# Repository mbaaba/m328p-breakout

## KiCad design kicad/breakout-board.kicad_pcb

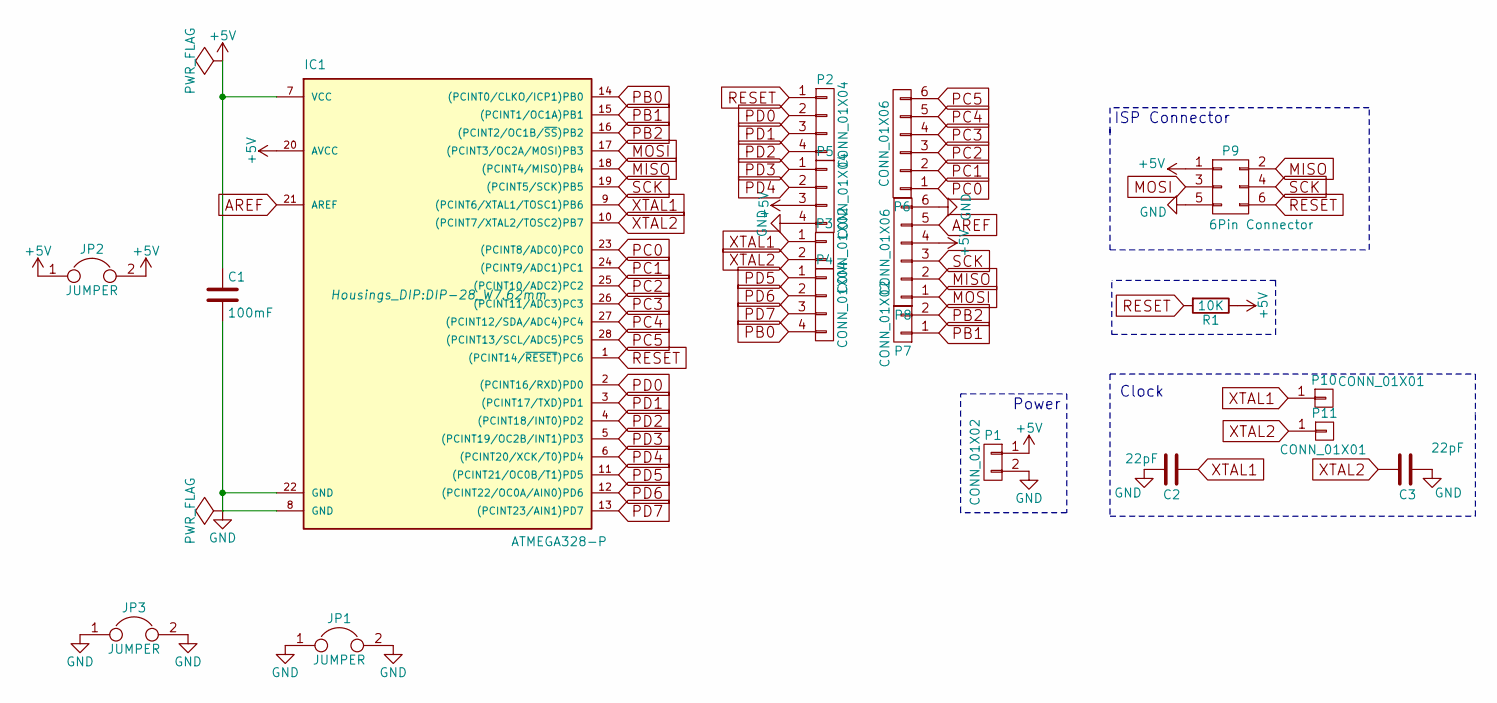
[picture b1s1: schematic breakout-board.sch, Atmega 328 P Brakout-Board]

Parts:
C1: 100mF; C_Disc_D3_P2.5
C2, C3: 22pF; C_Disc_D3_P2.5
IC1: ATMEGA328-P; DIP-28_W7.62mm
JP1, JP2, JP3: JUMPER; Resistor_Horizontal_RM15mm
P1, P3, P7: CONN_01X02; Pin_Header_Straight_1x02
P2, P4, P5: CONN_01X04; Pin_Header_Straight_1x04
P6, P8: CONN_01X06; Pin_Header_Straight_1x06
P9: 6Pin Connector; Pin_Header_Straight_2x03
P10, P11: CONN_01X01; Pin_Header_Straight_1x01
R1: 10K; Resistor_Vertical_RM5mm

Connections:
+5V: C1.1, IC1.7 (VCC), IC1.20 (AVCC), JP2.1, JP2.2, P1.1, P5.3, P8.4, P9.1, R1.1
AREF: IC1.21 (AREF), P8.5
GND: C1.2, C2.2, C3.1, IC1.8 (GND), IC1.22 (GND), JP1.1, JP1.2, JP3.1, JP3.2, P1.2, P5.4, P8.6, P9.5
MISO: IC1.18 ((PCINT4/MISO)PB4), P8.2, P9.2
MOSI: IC1.17 ((PCINT3/OC2A/MOSI)PB3), P8.1, P9.3
PB0: IC1.14 ((PCINT0/CLKO/ICP1)PB0), P4.4
PB1: IC1.15 ((PCINT1/OC1A)PB1), P7.1
PB2: IC1.16 ((PCINT2/OC1B/~SS~)PB2), P7.2
PC0: IC1.23 ((PCINT8/ADC0)PC0), P6.1
PC1: IC1.24 ((PCINT9/ADC1)PC1), P6.2
PC2: IC1.25 ((PCINT10/ADC2)PC2), P6.3
PC3: IC1.26 ((PCINT11/ADC3)PC3), P6.4
PC4: IC1.27 ((PCINT12/SDA/ADC4)PC4), P6.5
PC5: IC1.28 ((PCINT13/SCL/ADC5)PC5), P6.6
PD0: IC1.2 ((PCINT16/RXD)PD0), P2.2
PD1: IC1.3 ((PCINT17/TXD)PD1), P2.3
PD2: IC1.4 ((PCINT18/INT0)PD2), P2.4
PD3: IC1.5 ((PCINT19/OC2B/INT1)PD3), P5.1
PD4: IC1.6 ((PCINT20/XCK/T0)PD4), P5.2
PD5: IC1.11 ((PCINT21/OC0B/T1)PD5), P4.1
PD6: IC1.12 ((PCINT22/OC0A/AIN0)PD6), P4.2
PD7: IC1.13 ((PCINT23/AIN1)PD7), P4.3
RESET: IC1.1 ((PCINT14/~RESET~)PC6), P2.1, P9.6, R1.2
SCK: IC1.19 ((PCINT5/SCK)PB5), P8.3, P9.4
XTAL1: C2.1, IC1.9 ((PCINT6/XTAL1/TOSC1)PB6), P3.1, P10.1
XTAL2: C3.2, IC1.10 ((PCINT7/XTAL2/TOSC2)PB7), P3.2, P11.1

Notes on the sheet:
ISP Connector
Power
Clock

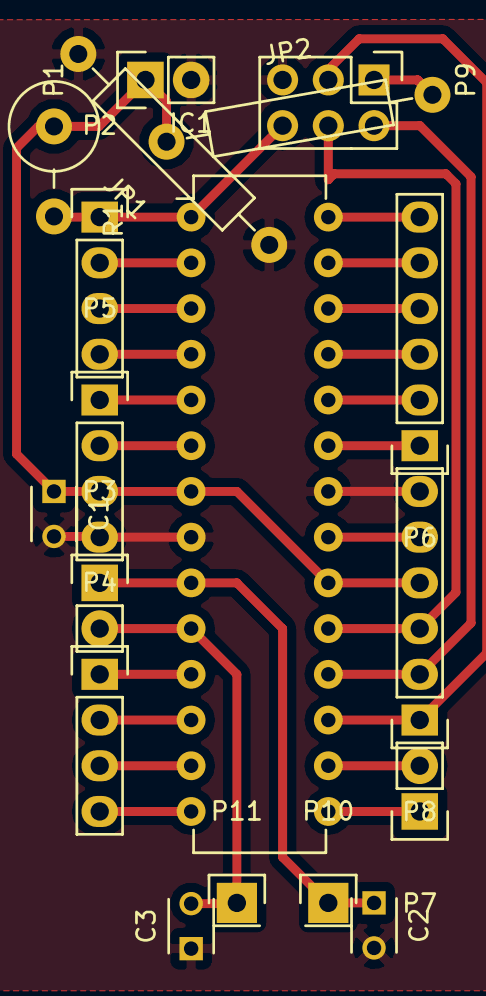
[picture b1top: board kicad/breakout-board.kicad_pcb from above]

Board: 2 copper layers, 18 parts (0 on the bottom side), 26 nets.

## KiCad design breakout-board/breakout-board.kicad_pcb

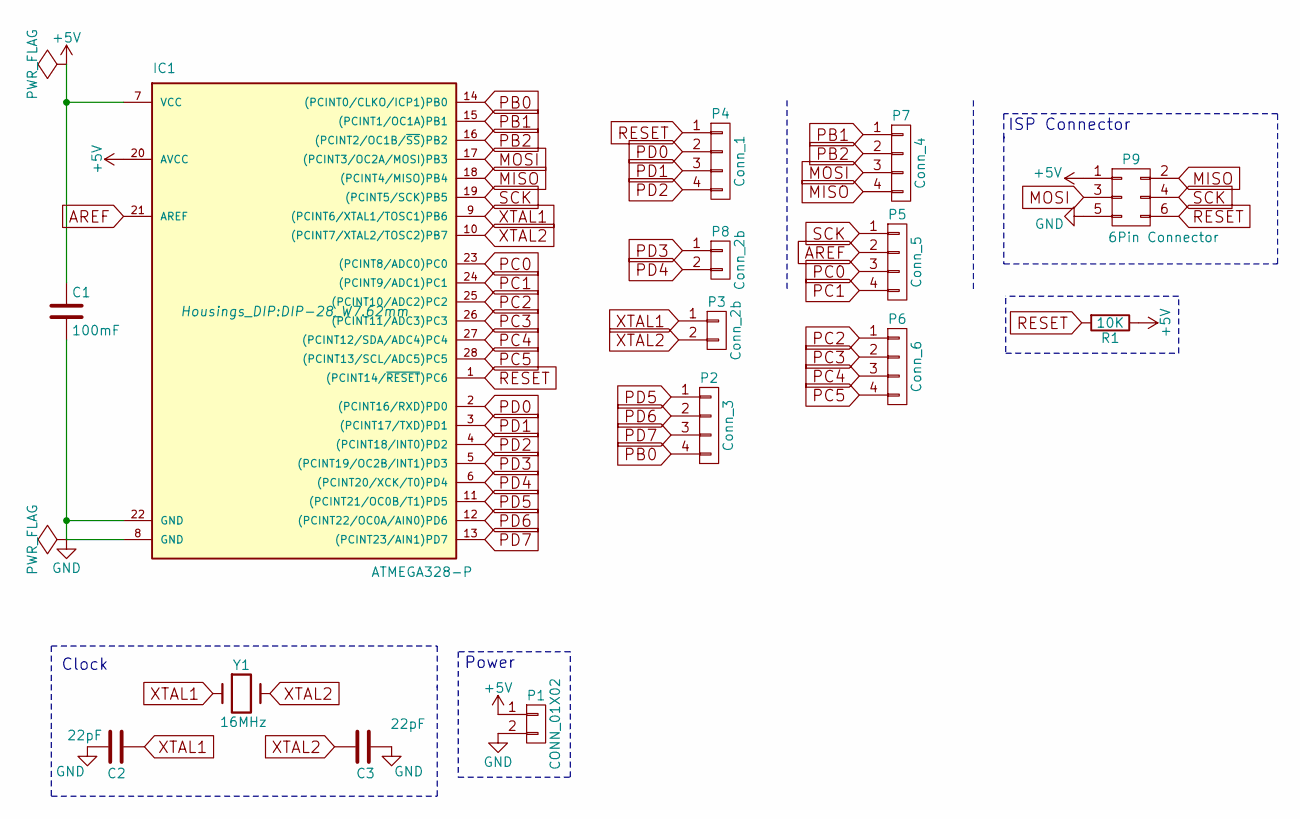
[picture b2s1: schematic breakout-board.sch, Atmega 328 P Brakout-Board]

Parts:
C1: 100mF; C_Disc_D3_P2.5
C2, C3: 22pF; C_Disc_D3_P2.5
IC1: ATMEGA328-P; DIP-28_W7.62mm
P1: CONN_01X02; Pin_Header_Straight_1x02
P2: Conn_3; Pin_Header_Straight_1x04
P3, P8: Conn_2b; Pin_Header_Straight_1x02
P4: Conn_1; Pin_Header_Straight_1x04
P5: Conn_5; Pin_Header_Straight_1x04
P6: Conn_6; Pin_Header_Straight_1x04
P7: Conn_4; Pin_Header_Straight_1x04
P9: 6Pin Connector; Pin_Header_Straight_2x03
R1: 10K; Resistor_Vertical_RM5mm
Y1: 16MHz; Crystal_HC50-U_Vertical

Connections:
+5V: C1.1, IC1.7 (VCC), IC1.20 (AVCC), P1.1, P9.1, R1.1
AREF: IC1.21 (AREF), P5.2
GND: C1.2, C2.2, C3.1, IC1.8 (GND), IC1.22 (GND), P1.2, P9.5
MISO: IC1.18 ((PCINT4/MISO)PB4), P7.4, P9.2
MOSI: IC1.17 ((PCINT3/OC2A/MOSI)PB3), P7.3, P9.3
PB0: IC1.14 ((PCINT0/CLKO/ICP1)PB0), P2.4
PB1: IC1.15 ((PCINT1/OC1A)PB1), P7.1
PB2: IC1.16 ((PCINT2/OC1B/~SS~)PB2), P7.2
PC0: IC1.23 ((PCINT8/ADC0)PC0), P5.3
PC1: IC1.24 ((PCINT9/ADC1)PC1), P5.4
PC2: IC1.25 ((PCINT10/ADC2)PC2), P6.1
PC3: IC1.26 ((PCINT11/ADC3)PC3), P6.2
PC4: IC1.27 ((PCINT12/SDA/ADC4)PC4), P6.3
PC5: IC1.28 ((PCINT13/SCL/ADC5)PC5), P6.4
PD0: IC1.2 ((PCINT16/RXD)PD0), P4.2
PD1: IC1.3 ((PCINT17/TXD)PD1), P4.3
PD2: IC1.4 ((PCINT18/INT0)PD2), P4.4
PD3: IC1.5 ((PCINT19/OC2B/INT1)PD3), P8.1
PD4: IC1.6 ((PCINT20/XCK/T0)PD4), P8.2
PD5: IC1.11 ((PCINT21/OC0B/T1)PD5), P2.1
PD6: IC1.12 ((PCINT22/OC0A/AIN0)PD6), P2.2
PD7: IC1.13 ((PCINT23/AIN1)PD7), P2.3
RESET: IC1.1 ((PCINT14/~RESET~)PC6), P4.1, P9.6, R1.2
SCK: IC1.19 ((PCINT5/SCK)PB5), P5.1, P9.4
XTAL1: C2.1, IC1.9 ((PCINT6/XTAL1/TOSC1)PB6), P3.1, Y1.1
XTAL2: C3.2, IC1.10 ((PCINT7/XTAL2/TOSC2)PB7), P3.2, Y1.2

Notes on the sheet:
ISP Connector
Power
Clock

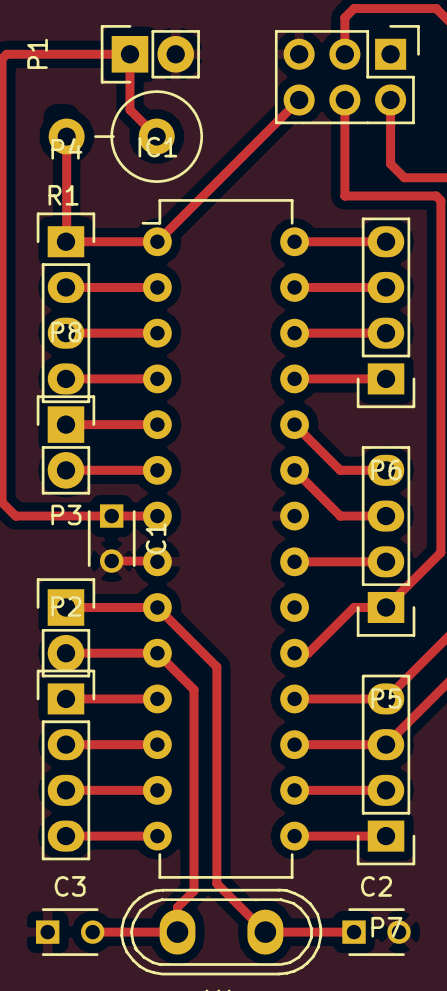
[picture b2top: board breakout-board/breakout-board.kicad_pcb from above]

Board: 2 copper layers, 15 parts (0 on the bottom side), 26 nets.

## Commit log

2016-01-08 initial commit without jumper wire
2016-01-09 kicad with jumper, flatcam gcode
2016-01-18 mirror gerber for gcode
2016-01-22 redesign fully header connected
2016-01-23 redesign mirror and re-place isp, make it smaller
2018-04-29 dont know
